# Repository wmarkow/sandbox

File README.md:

# sandbox
A sandbox reprository for my various projects.

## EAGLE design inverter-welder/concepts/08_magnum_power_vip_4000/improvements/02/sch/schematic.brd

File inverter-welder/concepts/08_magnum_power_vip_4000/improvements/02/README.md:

# Przeróbka spawarki Magnum Power VIP4000 na MIG

## Istota problemu: obniżenie napięcia biegu jałowego i napięcia spawania

Interesującym pomysłem jest przerobienie spawarki elektrodowej (MMA) na spawarkę typu MIG/MAG. Sprawa nie jest prosta gdyż spawarka
elektrodowa cechuje się sterowaniem prądowym (automat pilnuje nastawy pradowej) podczas gdy spawarki MIG/MAG pilnują nastawy napięciowej.
Z drugiej strony sprawa nie jest aż tak tragiczna i została poruszona w kilku miejscach, zwłaszcza na forum elektroda.pl na przykład
tutaj:

 * [Spawarka inwertorowa jako źródło migomatu?](https://www.elektroda.pl/rtvforum/topic688745.html)
 * [Spawarka mig mag z inwertera czy da rade ? ](https://www.elektroda.pl/rtvforum/topic1481430.html)
 * [Nakładka MIG do spawarki inwertorowej?](https://www.elektroda.pl/rtvforum/topic2955459.html)
 * [Poszukuję chętnego do przerobienia spawarki inwertorowej](https://www.elektroda.pl/rtvforum/topic2409633.html)
 * [dedra 200 przeróbka na miga czy możliwe jest zastosowanie te](https://www.elektroda.pl/rtvforum/topic959926.html)
 * [Przeróbka spawarki inwertorowej MMA na MIG-MAG](https://forum.elportal.pl/viewtopic.php?t=13849)

Kilku użytkowników forum wskazuje, że można spróbować podłączyć palnik MIG wraz z podajnikiem drutu bezpośrednio
do wyjścia spawarki elektrodowej i po prostu spróbować. Nie zawsze kończy się to sukcesem. Problemem okazuje się
również zbyt wysokie napięcie biegu jałowego w spawarkach elektrodowych, które mieści się w granicach 60-70V (zależy od
modelu urządzenia).
Tak wysokie napięcie powoduje szybkie upalanie się drutu spawalniczego, zwłaszcza w początkowej fazie spawania,
gdzie mechanizm regulacji prądowej nie zdążył jeszcze zareagować (regulacja prądu wyjsciowego odbywa sie na zasadzie
obniżenia napięcia wyjściowego: im niższe napięcie wyjsciowe tym mniejszy prąd na wyjsciu) i przez krótki moment do
drutu spawalniczego podłączone jest wysokie napięcie jałowe.
Sam dokonałem takiej próby: podłączyłem prowizoryczny palnik MIG typu SpoolGun (zbudowany na szybko tylko w celu wykonania doświadczenia).
Rzeczywiście, przy próbie spawania końcówka drutu bardzo szybko się rozgrzewa do czerwoności i upala się przy końcówce prądowej
palnika. Następuje wtedy stan rozwarcia, spawarka wykrywa brak przepływu prądu (bo drut nie styka się już
z materiałem spawanym) i przechodzi w tryb biegu jałowego, gdzie napięcie na wyjściu znów jest wysokie w ok. 60-70V. Po pewnej
chwili stale wysuwający się drut ponownie dotyka materiału spawanego, zaczyna przepływać prąd, drut się rozgrzewa (wysokie napięcie
jałowe), być może przez chwilę automat ogranicza na moment napięcie wyjsciowe by ustalić przepływ ustalonego prądu, ale często
jest już za późno, gdyż drut ponownie się upala przy końcówce prądowej, i cykl się powtarza. Generalnie nie idzie spawać.
Często się zdarza, że drut stapia się z końcówką prądową. Przestaje wtedy działać posów drutu a końcówka prądowa nadaje się
najczęściej do wymiany.

## Symulacja regulacji napięcia: układ z potencjometrem podłączonym do pinu 8 układu SG3525

Zainspirowany różnymi amatorskimi konstrukcjami spawarek MMA/MIG/MAG w szczególności [Invertor popis](https://github.com/wmarkow/sandbox/blob/master/inverter-welder/concepts/09_mma_mig_mag/invertor_popis.pdf),
postanowiłem podjąć kroki by mimo wszystko spróbować dokonać przeróbki spawarki elektrodowej inwertorowej na MIG/MAG. Moja spawarka **Magnum Power VIP 4000** jest
oparta o układ scalony **SG3525**. Po przejrzeniu [noty katalogowej](https://github.com/wmarkow/sandbox/blob/master/inverter-welder/elements/sg3525/SG1525.pdf) postanowiłem [zbadać jego zachowanie](https://github.com/wmarkow/sandbox/blob/master/inverter-welder/elements/sg3525/tests/README.md) w różnych układach konfiguracyjnych.
W kontekście obniżenia napięcia biegu jałowego szczególnie interesujący jest [Test 4: limit PWM duty cycle with Soft-Start pin](https://github.com/wmarkow/sandbox/blob/master/inverter-welder/elements/sg3525/tests/Test4/README.md),
gdzie wykorzystany został Pin 8 układu (tzw. Soft Start) do ograniczenia przebiegu PWM na wyjściu układu. To rozwiązanie jest godne uwagi ze względu na bezinwazyjność w układ sterowania spawarki; wystarczy wlutować jeden dodatkowy potencjometr. 

Schemat układu symulacji został przedstawiony na rysunku poniżej. Po lewej stronie znajduje się
orginalny układ spawarki: kondensator C32 i rezystor R40 podłączone do pinu 8 układu SG3525. Razem
z wewnetrznym źródłem prądowym 50uA realizują one układ tzw. "miękkiego startu". Dopóki napięcie
na pinie 8 jest mniejsze od 0.9V, dopóty ukłąd generuje sygnały PWM o wypełnieniu 0%. Gdy napięcie
jest wyższe od 3.3V to ukad generuje sygnały o wypełnieniu 49%. Poziomy napięć pomiędzy 0.9V a 3.3V
generują sygnały PWM o wypełnieniu od 0% do 49%. Tak rzecze dokumentacja układu SG3525. Po włączeniu
zasilania układ "miękkiego startu" powoli rozkręca układ do generacji maksymalnego wypełnienia.
Dodatkowym potencjometrem (schemat po prawej) można ustalić w miarę dowolne napięcie na pinie 8, 
co pozwoli z góry ograniczyć napięcie na biegu jałowym lub spawania. 

Symulacja pokazuje wpływ takiego rozwiązania na układ "miękkiego
startu". Wykres napięć w obu przypadkach (bez modyfikcji kolor zielony i z modyfikacją kolor niebieski) poniżej:

pokazuje, że modyfikacja spowalnia rozruch urządzenia prawie dwukrotnie (na maksymalnym ustawieniu potencjometru):
* bez modyfikacji układ osiąga PWM 49% (napięcie 3.3V) po około 45ms. Kondensator ładuje się liniowo ze źródła prądowego.
* z modyfikacją układ osiąga PWM 49% (napięcie 3.3V) po około 75ms. Ponadto obecność potencjometru zmienia charakterystykę ładowania
kondensatora z liniowej na wykładniczą.

Wydaje mi się, że takie spowolnienie nie ma negatywnego wpływu na pracę urządzenia. Gorzej by było,
gdyby modyfikacja przyspieszyła rozruch.

## Próba z potencjometrem podłączonym do pinu 8 układu SG3525

Zmontowany układ pomiarowy wygląda tak:

Na zdjęciu widać podlutowany odpowiednio potencjometr (wartość 88k zmierzona miernikiem), zaciski prądowe, multimetr i ... podłączoną do zacisków żarówkę.
Żarówka wstępnie obciąża układ względnie niską rezystancją. Występuje na niej napięcie ok 61V i przepływa
przez nią prąd ok 50mA (przy potencjometrze ustawionym na wartość maksymalną) [^1]. Bez tej żarówki napięcie wyjściowe na zaciskach jest mniej więcej stałe i wynosi około
62V bez wględu na wartość nastawy potencjometru. Innymi słowy wartość wypełnienia generowanego sygnału PWM się zmienia, ale napięcie
na wyjściu **wskazywane multimetrem** (to jest ważne) jest stałe. Okazuje się, że spawarka w obwodzie wyjściowym
ma kondensatory, które są ładowane ze źródła. Wyjście spawarki jest już "wstępnie obciążone" dzielnikiem
rezystancyjnym (o wartości 23.4k) służącym do pomiaru napięcia wyjściowego i wykrywania stanu zwarcia elektrody.
Ten dzielnik rezystancyjny powoduje powolne rozładowanie kondensatorów wyjściowych, dlatego napięcie wskazywane
przez multimer jest mniej więcej stałe bez względu na wartość wypełnienia sygnału PWM; napięcie zauważalnie maleje dopiero przy niskich
wypełnieniach PWM. Podłączona żarówka ma za zadanie wstępnie obciążyć układ małą rezystancją (małą w porównaniu
z dzielnikiem napięcia ale wysoką od rezystancji łuku spawalniczego), co spowoduje szybsze rozładowanie kondensatorów i multimetr "zauważy" spadek napięcia
wyjściowego.
  
Nastawę potencjometru określiłem sobie w godzinach, zgodną z tarczą wskazówek zegarka, jak na zdjęciu poniżej:

Wyniki pomiarów znajdują się w tabelce poniżej:

 | Nastawa potencjometru [h] | Zmierzone napięcie wyjściowe przy rozłączonej żarówce [V] | Zmierzone napięcie wyjściowe przy załączonej żarówce [V]| Zmierzone napięcie na potencjometrze [V]| Zmierzona oporność na potencjometrze [kOhm]| Obliczony PWM [%]| Obliczone napięcie wyjściowe [V]|
 |---|---|---|---|---|---|---|
 |   max | 61.9 | 60.4 | 3.7 | 88.5 | 49 | 62 |
 |    15 | 61.4 | 59.5 | 3.1 | 74.6 | 45 | 57 |
 |    12 | 59.8 | 53.7 | 1.8 [^2] | 39.6 | 18 | 23 |
 |    11 | 59.7 | 52.4 | 1.5 | 34.0 | 12 | 15 |
 | 11/10 | 20.0 |  8.9 | 1.2 | 27.8 |  6 |  8 |
 |    10 | 10.0 |  0.0 | 0.9 | 19.9 |  0 |  0 |
 |     9 | 10.0 |  0.0 | 0.6 | 11.5 |  0 |  0 |
 |   min | 10.0 |  0.0 | 0.0 |  |  0 |  0 |

Potencjometr okazuje się działać ale jednak nieliniowo. Bardzo łatwo jest zbić napięcie do zmierzonej wartości około 45V. Później
dalsza minimalna zmiana nastawy skutkuje szybkim spadkiem napięcia do 0V. Udało mi się uzyskać zmierzone napięcie wyjściowe
35V a potencjometr był ustawiony wtedy na 27.5k (nastawa gdzieś pomiędzy godziną 10 a 11).

Nadmienię jeszcze raz fakt pomiaru napięcia multimetrem. Przy rozłączonej żarówce multimetr nie zauważa zbytniego spadku napięcia
wyjściowego. Jest to spowodowane obecnością dużej wstępnej rezystancji obciążającej (23.4k) układ i powodującej
powolne rozładowywanie kondensatorów wyjsciowych. Przy załączonej żarówce o oporności około nieco ponad 1k multimetr
łatwiej zauważa spadek napięcia wyjściowego. Jednak ten pomiar multimetrem równiez należy traktować tylko jako **pomiar
orientacyjny!** Prawdziwa wartość napięcia ujawnia się dopiero podczas procesu spawania, gdzie rezystancja obciążenia jest
na prawdę niska i prawie bliska rezystancji zwarciowej. Dlatego w tabelce powyżej zamieściłem kolumny pomocnicze:
* **PWM** zawierającą wyliczoną - na podstawie napięcia na pinie 8 układu SG3525 - wartośc wypełnienia genarowanych
sygnałów PWM. Wartość 49% oznacza generowanie maksymalnego napięcia (ok. 62V), wartość 0% oznacza minimalne
napięcie na wyjściu (ok 0V).
* **Obliczone napięcie wyjściowe** - wyznaczone na podstawie wartości wypełnienia **PWM**. Wartość tego napięcia
należałoby traktować jako wyrocznię, gdyż ta wartość ujawnia się podczas procesu spawania.

Widać, że regulacja napięcia biegu jałowego działa. Trzeba by wykonać próbę spawania. Aby polepszyć zakres
regulacyjny potencjometru, proponuję zamienić go na opornik około 33k połączony szeregowo z potencjometrem 
o wartości ok. 56k. Powinno być wtedy możliwe bardziej selektywne regulowanie napięcia biegu jałowego w zakresie ok. 15V-60V.
Warto by było przeprowadzić test ze zmniejszoną opornością obciążenia wstępnego (żarówki). W przeprowadzonym teście żarówka miała opór
ciut większy od 1k, być może warto by było zastosować tutaj jakiś rezystor dużej mocy o oporności np. 200 Ohm?

Ciekawostką jest fakt, że przy rozłączonej żarówce i napięciu na pinie 8 mniejszym od 0.9V, napięcie zmierzone na wyjściu spawarki jest 10V.
Dopiero przy załączonej żarówce spada do 0V.

## Pierwsze testowe spoiny

Na potrzeby testu zbudowałem prowizoryczny uchywt typu spool-gun:

Jest bardzo nieporęczny ale daje radę podczas testów. W skład konstrukcji wchodzą:
* końcówka palnika wraz z końcówką prądową przymontowane taśmą do długiej na ok. 40cm pilśniowej listwy. Do tej końcówki bezpośrednio
jest "zapięty" uchwyt elektrodowy podłączony do zacisku masowego spawarki, gdyż spawanie odbywa się z użyciem drutu proszkowego, gdzie producent zaleca,
że drut musi być podpięty do zacisku masowego. 
* podajnik drutu zrobiony z silnika krokowego NEMA 17 i ekstrudera filamentu od drukarki 3D. Silnik krokowy zapewnia odpowiedni posuw drutu. Ekstruder posiada
koło zębate (założone bezpośrednio na wał silnika) oraz element dociskowy z małego łożyska. Generalnie okazuje się to działać poprawnie. Minusem rozwiązania
jest zbyt duża waga silnika zwiększająca ciężar całego uchwytu.
* szpulka z drutem założona bezpośrednio na wkręconą w pilśniowa listwę śrubę M8. Szpulka zabezpieczona jest przed wypadnięciem nakrętką M8.
* wyłącznik krańcowym służy jako włącznik podajnika drutu
* Arduino UNO wraz z "nakładką CNC" reaguje na naciśnięcie wyłącznika krańcowego i steruje wtedy silnikiem krokowym
* potencjometr zamontowany do "nakładki CNC" służący do regulacji szybkości posuwu drutu w zakresie od 0 do 200 cm/min. 

Pierwsze próby pięciu spoin na zdjęciach poniżej. Generalnie zaczynałem od minimalnej nastawy napięcia 35V (uwaga: wartość zmierzona multimetrem - traktować tylko orientacyjnie ze względu na niedostatecznie niską
rezystancję żarówki) i minimalnej nastway prądu 100A.
Prędkość wysuwu drutu szybko ustawiłem na 200cm/min, gdyż przy mniejszych wartościach wysuwu wychodziły tylko poprzerywane krople (z prawej strony
zdjęć). Próba numer 1 okazała się mieć za niskie napięcie lub za niski prąd. Przy próbce 2 już zwiększyłem nastawę prądu do 140A. Nastawy
napięcia niestety nie zanotowałem. Generalnie przy kolejnych próbach zacząłem zwiększać nastawy prądu i napięcia,
aż przy próbce numer 4 i 5 spoina zaczęła się wtapiać w materiał podstawowy. Z lewej strony nieudolnie wspawana nakrętka.

## Kolejne testowe spoiny

Po pierwszych próbach testowych ponownie obejrzałem filmik na Youtube [How NOT TO Weld: Most Common MIG Welding Mistakes](https://www.youtube.com/watch?v=Xod-ByrxHg4), 
objaśniający podstawowe typy błędów w spawaniu MIG. Skupiłem się na prędkości wysuwu drutu spawalniczego. Optymalną prędkością na filmiku była 200 cali/min (czyli ok 500 cm/min),
podczas gdy ja używałem tylko 200 cm/min. Zmodyfikowałem program Arduino i już pseudo spool-gun był gotowy do pracy z wysuwem drutu w zakresie 0-500 cm/min.
Zdjęcia spoin testowych poniżej:

Prąd spawania ustawiłem na 200A (maksymalna nastawa spawarki) a napięcie biegu jałowego ograniczone zostało potencjometrem
do poziomu 55V (uwaga: wartość zmierzona multimetrem - traktować tylko orientacyjnie ze względu na niedostatecznie niską
rezystancję żarówki). Obliczona wartość napięcia wyjściowego dla tej nastawy - według tabelki powyżej - byłaby około 30V. Tym razem spoiny wyglądaja dużo lepiej. Widać wtopienie w materiał podstawowy. Próby 1 i 2 szły bez problemu.
W próbie 3 postanowiłem zmniejszyć nastawę prądu do 100A i zacząłem odczuwać odpychanie uchwytu od materiału podstawowego.
Prawdopodobnie zbyt niski prąd nie nadążał topić drutu wysuwanego z tak dużą prędkością. Średnia długość spoin na zdjęciach
to około 3-4 cm. Funkcja anti-stick spawarki wydawała się nie mieć negatywnego wpływu na proces spawania; na razie nie widzę 
potrzeby rozłączania tego mechanizmu podczas spawania MIG.

## Symulacja regulacji napięcia: układ ze sprzężeniem zwrotnym podłączony do pinu 8 układu SG3525

Ciekawy układ regulacji napięcia wyjściowego został przytoczony w [tym poście na forum](https://www.elektroda.pl/rtvforum/viewtopic.php?p=19978221#19978221).
Schemat zaczerpnięty prawdopodobnie z rosyjskojęzycznej strony Internetu:

Kilka słów wyjasnienia:
* zaciski K+ i K- to najprawdopodobniej zaciski wyjściowe spawarki
* potencjometr 10k służy do nastawy napięcia wyjściowego
* przełącznik MMA/MIG-MAG służy do przełączania sterownika w tryb MMA lub MIG-MAG
* przekaźnik na dole po lewej jest załączany przyciskiem w uchwycie MIG. W stanie normalnym przycisk nie jest wciśnięty
(nie ma spawania) i wyjście przekaźnika zwiera pin 8 układu SG3525 do masy i napięcie na wyjściu spawarki jest 0V. Po wciśnięciu
przycisku w uchwycie (rozpoczęcie procesu spawania) przekaźnik się załącza i odcina pin 8 od masy, następuje włączenie napięcia
spawania.
* optoizolator PC817 zapewnia izolację galwaniczna pomiędzy obwodem spawania a obwodem sterowania SG3525, a jednocześnie steruje
napięciem na pinie 8

Przygotowałem symulację tego układu w programie LTSpice. Schemat układu jest następujący:

Symulacja układu polega na wymuszonej zmianie napięcia spawania w zakresie od 0 do 60V i obserwacji jej wpływu na napięcie pinu 8.
Wynik symulacji przedstawia sie następująco:

Analiza:
* potencjometr nastawy napięcia ustawiony w pozycji środkowej (nastawa na 30V)
* jeżeli napięcie spawania spadnie poniżej ok. 29V to napięcie na pinie 8 jest 5V, co spowoduje generowanie sygnałów
PWM o wypełnieniu 49% i wzrost napięcia wyjściowego w kierunku wartości maksymalnej 60V
* jeżeli napięcie spawania wzrośnie powyżej ok. 29V to napięcie na pinie 8 jest 0V, co spowoduje generowanie sygnałów
PWM o wypełnieniu 0% i spadek napięcia wyjściowego w kierunku wartości minimalnej 0V
* w układzie wystepuje sprzężenie zwrotne, które dąży do ustabilizowania napięcia na zadanym poziomie
* stabilizacja napięcia jest raczej dwustabilna: albo spawarka podaje napięcie maksymalne albo minimalne. Takie cykliczne
zmiany stabilizują napięcie wyjściowe na średnim zadanym poziomie. Nasuwa się pytanie czy taki dwustabilny tryb pracy jest
dobry dla procesu spawania lub spawarki. Można przecież wysterować pin 8 napięciem pośrednim (np. 2.5V) co wygeneruje
pośrednie napięcie spawania.
* na powyższym wykresie tego nie widać, ale regulacja napięcia wyjściowego jest w zakresie od 20 do 40V.

Powyższego układu nie testowałem w praktyce. Tylko zasymulowałem jego działanie.

## Ciekawostka:
* test z wyłączoną żarówką
  * wyłączyć spawarkę
  * upewnić się, że żarówka jest wykręcona
  * upewnić się, że potencjometr biegu jałowego jest ustawiony w pozycję maksymalną (czyli nie działa ograniczanie napięcia biegu jałowego)
  * włączyć spawarkę
  * zmierzyć miernikiem napięcie na zaciskach wyjściowych: u mnie było ono 61V
* test z włączoną żarówką
  * wyłączyć spawarkę
  * upewnić się, że żarówka jest wkręcona
  * upewnić się, że potencjometr biegu jałowego jest ustawiony w pozycję maksymalną (czyli nie działa ograniczanie napięcia biegu jałowego)
  * włączyć spawarkę
  * zmierzyć miernikiem napięcie na zaciskach wyjściowych: u mnie było ono 0V!
  * wykręcić żarówkę (żeby nie obciążać nią wyjścia spawarki)
  * wkręcić żarówkę ponownie
  * zmierzyć miernikiem napięcie na zaciskach wyjściowych: teraz było ono 61V!
 
Wygląda, jakby układ spawarki wykrywał, że podczas jej uruchomienia było podłączone jakieś obciążenie; w takim przypadku - prawdopodobnie - układ SG3225 jest w stanie
zamknięcia (odcięcia) i generuje on sygnał PWM o zerowym wypełnieniu. Być może jest to jakieś dodatkowe zabezpieczenie. W tym konkretnym przypadku, żadne diody sygnałowe
na panelu urządzenia nie były zapalone.

[^1]: Co by wskazywało, że opór podłączonej żarówki jest 1.22k
[^2]: Napięcie na potencjometrze jest jednocześnie napięciem na pinie 8 układu SG3525. Napięcie 1.8V generuje
sygnał PWM o wypełnieniu około 18%, co powinno generować napięcie 22V. Tymczasem multimetr wskazuje zawyżone napięcie 53.7V.
Być może oporność żarówki 1.22k jest jeszcze zbyt duża i wyjście spawarki nie jest dostatecznie szybko rozładowywane?

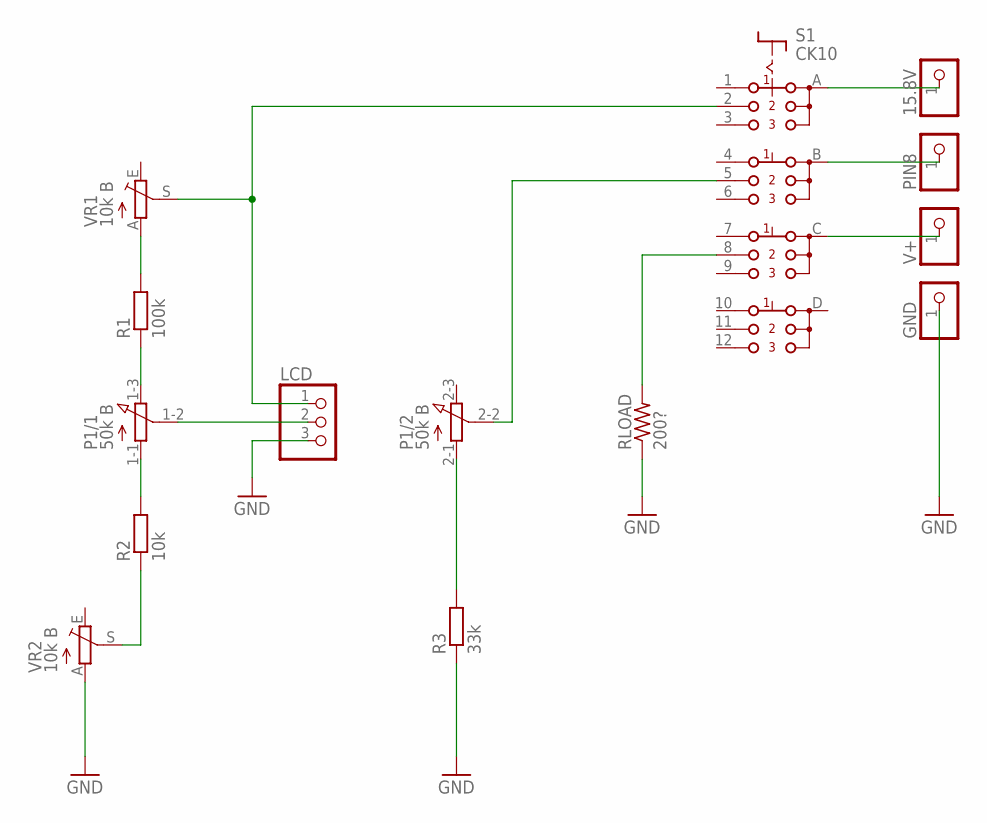
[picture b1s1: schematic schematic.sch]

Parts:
15.8V: PINHD-1X1; 1X01
GND: PINHD-1X1; 1X01
LCD: PINHD-1X3; 1X03
P1: 50k B; 3RP/1610G
PIN8: PINHD-1X1; 1X01
R1: 100k; 0204/5
R2: 10k; 0204/5
R3: 33k; 0204/5
RLOAD: 200?; VTA52
S1: CK10
V+: PINHD-1X1; 1X01
VR1, VR2: 10k B; RJ9W

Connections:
GND: GND.1, LCD.3, R3.1, RLOAD.1, VR2.A
unnamed: P1.2-2 (S), S1.5 (B2)
unnamed: 15.8V.1, S1.A
unnamed: PIN8.1, S1.B
unnamed: P1.1-1 (A), R2.2
unnamed: P1.1-3 (E), R1.1
unnamed: LCD.1, S1.2 (A2), VR1.S
unnamed: R1.2, VR1.A
unnamed: LCD.2, P1.1-2 (S)
unnamed: R2.1, VR2.S
unnamed: S1.C, V+.1
unnamed: RLOAD.2, S1.8 (C2)
unnamed: P1.2-1 (A), R3.2

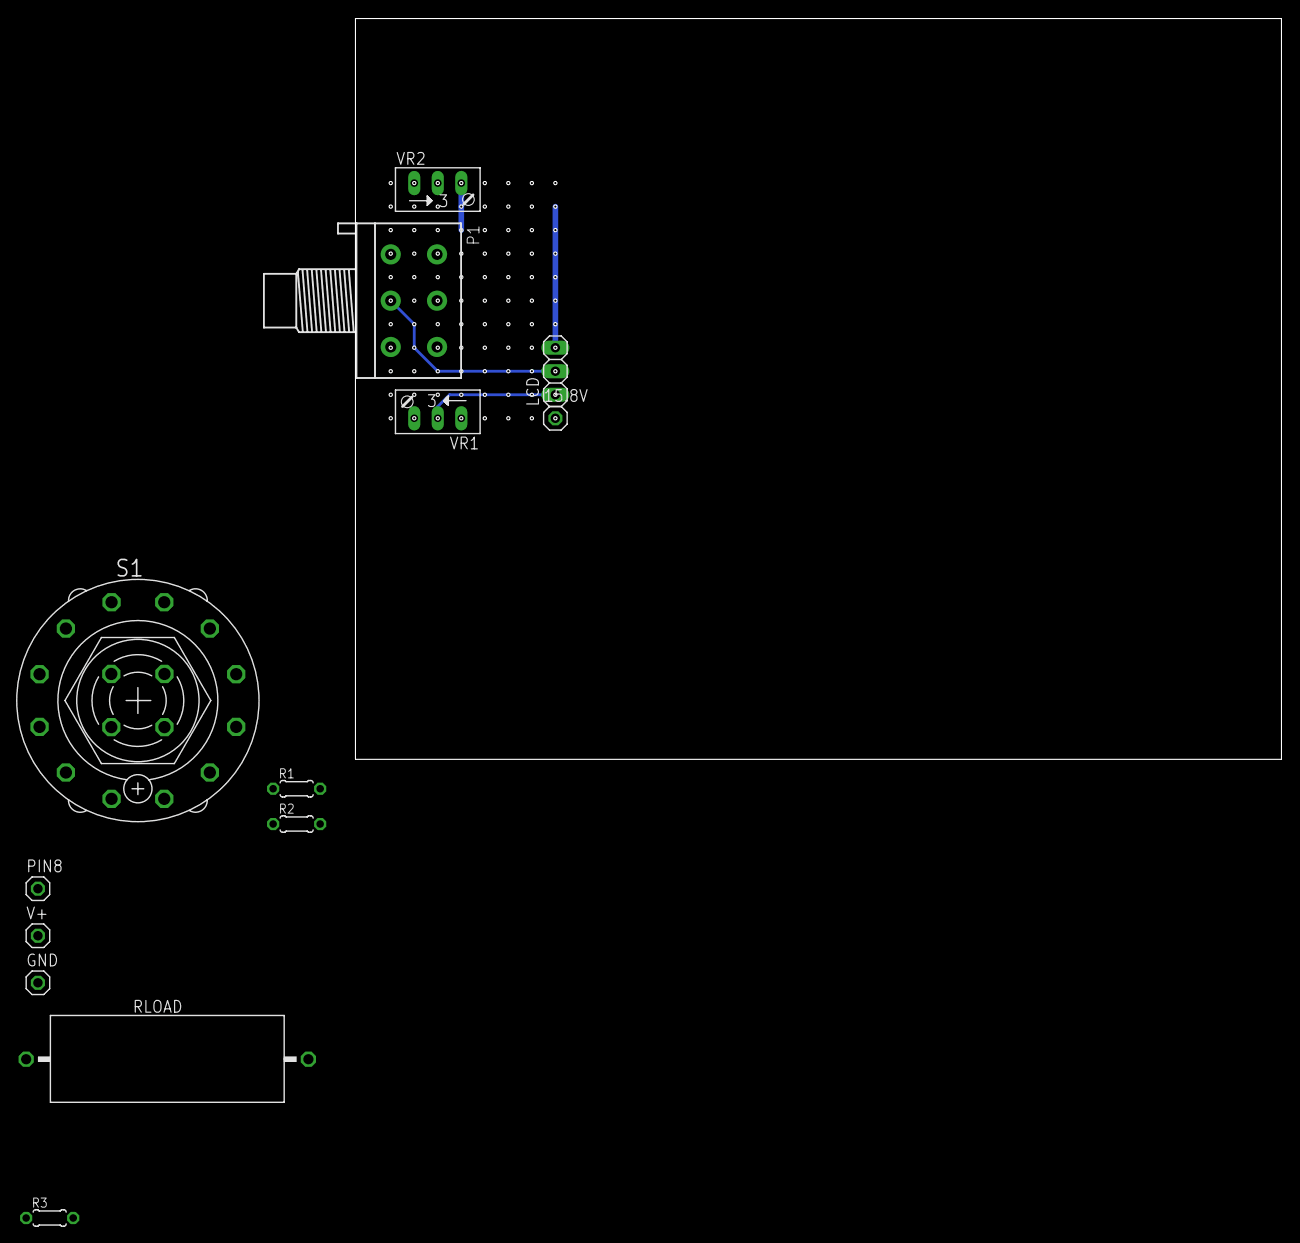
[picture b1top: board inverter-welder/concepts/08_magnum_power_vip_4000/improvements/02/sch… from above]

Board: 2 copper layers, 100.0 x 80.0 mm, 13 parts (0 on the bottom side), 13 nets.

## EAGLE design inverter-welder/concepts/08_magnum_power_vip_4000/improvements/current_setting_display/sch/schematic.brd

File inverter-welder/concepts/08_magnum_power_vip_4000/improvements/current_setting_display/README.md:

# Przeróbka spawarki Magnum Power VIP4000: dodanie wyświetlacza panelowego

Postanowiłem wzbogacić moją spawarkę o wyświetlacz panelowy, który wyświetlałby aktualną nastawę prądu spawania. Sam potencjometr ze skalą w zasadzie wystarczy
ale jak się później okazało, wyświetlacz ma również swoją zaletę: można precyzyjniej ustawić wartość prądu spawania. Pewnego razu musiałem używać na zmianę
elektrod o grubości 1.6mm i 2.0mm. Eksperymentalnie doszedłem do wniosku, że w tej konkretnej aplikacji elektrodą 1.6mm spawa mi się najlepiej prądem ok 33A
a do elektrody 2.0mm potrzebuję prądu spawania 45A. Wyświetlacz panelowy bardzo ułatwił mi przełączanie się pomiędzy elektrodami. Polegając tylko na samej skali
potencjometru nie byłbym w stanie uzyskać tych dwóch konkretnych nastaw prądu.

Zastosowany wyświetlacz dla kilku nastaw przedstawia się następująco:

a zamontowany w spawarce układ wygląda tak:

<br/>

## Idea układu
Rozwiązanie techniczne wyświetlacza polega na zastąpieniu orginalnego potencjometru nastawy potencjometrem podwójnym oraz użyciu prostego woltomierza panelowego:
* pierwszy ślizgacz potencjometru służy do regulacji nastawy prądu i jest bezpośrednio wmontowany w układ spawarki (zamiast potencjometru orginalnego)
* drugi ślizgacz służy do wyświetlania wartości nastawy na woltomierzu panelowym

Ponieważ oba ślizgacze są regulowane jednocześnie za pomocą tej samej gałki to mamy pewność, że nastawa prądu jest zgodna z tym co przedstawia woltomierz panelowy. Układ został tak skalibrowany,
że przy nastawie minimalnej wyświetlacz pokazuje napięcie **0.20V** (co odpowiada nastawie 20A) a przy nastawie maksymalnej wyświetlacz pokazuje **2.00V** (co odpowiada
nastawie 200A). Skalibrowane nastawy bazują jedynie na tabliczce znamionowej podanej przez producenta. Nie ma pewności, że nastawa 200A rzeczywiście ustawia prąd spawania
na poziomie 200A, jednakże powtarzalność nastaw jest tutaj zapewniona. Oczywiście można wyświetlacz skalibrować również za pomocą cęgowego miernika prądu.

Przed przystąpieniem do prac dokonałem oględzin orginalnego potencjometru i jego okolic. Poniżej schemat układu, uzyskany metodą inżynierii odwrotnej:

Potenjometr nastawy (VRa + VRb) ma wartość **830** ohm a jego zaciski sa podłączone do trzech przewodów w kolorach czerwonym (przez VR1 i R79 do zasilania 15.8V), czarnym (wyjście nastawy) i zielonym (do masy).
Przewód czarny idzie bezpośrednio przez rezystory R71 i R55 a potem dalej do wzmacniacza operacyjnego, który odpowiedzialny jest za utrzymanie prądu spawania podczas procesu spawania.
Poniżej przedstawiam wartość napięcia na wyjściu potencjometryu (przewód czarny) w zależności od nastawy potencjometru:

 | Nastawa prądu [A] | Napięcie na wyjściu potencjometru (przewód czarny) [V] |
 |---|---|
 | min | 0.00 |
 |  20 | 0.00 |
 |  65 | 1.90 |
 | 110 | 3.53 |
 | 145 | 5.15 |
 | 200 | 6.48 |
 | max | 6.59 |

Projektując układ wyświetlacza należy za pomoca nowego potencjometru uzyskać takie same poziomy napięć na przewodzie w kolorze czarnym, wtedy układ nastawy będzie działał taki sam sposób, jak przewidział to producent.
Dobór odpowiednigo potencjometra podwójnego nie jest prosty; trzeba użyć potencjometru o wartości jak najbardziej zbliżonej do orginalnej. Na przykład użycie takiego o wartości 10k powoduje generowanie
dużo wyższych napięć, co spowoduje niepoprawną pracę urządzenia. Taki o wartości **830** ohm był dla mnie nieosiągalny i dlatego zdecydowałem się na najprostszy (co nie oznacza, że najlepszy) 
potencjometr **1k** jak na zdjęciu poniżej:

<br/>

## Schemat układu
Schemat nowego potencjometru nastawy wraz z wyświetlaczem panelowym poniżej:

**P1/2** to ślizgacz potencjometru wmontowanego bezpośrednio w spawarce zamiast orginalnego potencjometru. Ponieważ użyty przeze mnie potenjometr podwójny ma wartość **1k** (a orginalny
ma wartość **830** ohm), używam potencjometru VR3 o wartości **500** ohm by dostosować charakterystykę nowego potencjometru do tego orginalnego. Chodzi o to by przy minimalnej nastawie
uzyskać napięcie czarnego przewodu na poziomie 0.00V a przy maksymalnej nastawie uzyskać napięcie około 6.60V.

Potencjometr **P1/1** i rezystory nastawne **VR1** i **VR2** służą do regulcaji i wyświetlania napięcia na woltomierzu panelowym. VR1 i VR2 należy tak wyregulować aby:
* przy minimalnej nastawie woltomierz pokazywał **0.20** V
* przy maksymalnej nastawie woltomierz pokazywał **2.00** V

Montaż układu jest prosty:
* VR1 ustawić na wartość maksymalną 10k
* VR2 ustawić na wartość minimalną 0 ohm
* P1/1 ustawić na wartość maksymalną 1k
* VR3 ustawić na wartośc maksymalną 500 ohm
* podłączyć odpowiednio wyjścia złącza JP1 do przewodów w spawarce (zielony, czarny i czerwony). Zasilanie 15.8V znaleźć w spawarce za pmoocą woltomierza.
* podłączyć odpowiednio woltomierz panelowy do złącza LCD

<br/>

## Kalibracja trymera VR3:
1. uruchomić spawarkę
2. ustawić maksymalną nastawę prądu (200A)
3. zmniejszać wartość trymera VR3 aż do uzyskania napięcia na czarnym przewodzie na poziomie 6.60V
4. ustawić minimalną wartość nastawy prądu; napięcie na czarnym przewodzie powinno wynosić 0V

<br/>

## Kalibracja wyświetlacza:
1. uruchomić spawarkę
2. ustawić maksymalną nastawę prądu (200A)
3. zmieniać (generalnie zmniejszać) wartość trymera VR1 aż woltomierz pokaże 2.00V
4. ustawić minimalną nastawę prądu spawania (20A)
5. zmieniać (generalnie zwiększać) wartośc trymera VR2 aż woltomierz pokaże 0.20V
6. powtórzyć kroki od 2 do 5 kilka razy (zwykle 3 razy są wystarczające)
7. przy minimalnej nastawie woltomierz powinien pokazać 0.20 a przy maksymalnej nastawie powinien pokazać 2.00

W tym momencie wyświetlacz jest skalibrowany i powinien działać poprawnie. Mi przeszkadzała jeszcze kropka dziesiętna w woltomierzu panelowym. Aby jej nie wyświetlać to należy
przeciąć nóżkę sterującą (pin 3) w wyświetlaczu siedmiosegmentowym i złatwione (schemat [tutaj](https://raw.githubusercontent.com/wmarkow/sandbox/master/inverter-welder/concepts/08_magnum_power_vip_4000/improvements/current_setting_display/docs/3_digits_display.jpg)).
Z kropką dziesiętną wyświetlacz pokazuje tak:

natomiast bez kropki jest już o niebo lepiej:

<br/>

## Niedoskonałość skali
Jeszcze jedna uwaga o pewnej niedoskonałości całego rozwiązania: mianiowicie wskazania wyświetlacza nie pokrywają się ze wskazaniami orginalnej skali potencjometru. Wynika to z tego, że zastosowany
przeze mnie potenjometr ma większy kąt obrotu niż potencjometr orginalny. Być może można by coś w tej sprawie polepszyć, np. zastosować jakiś mechaniczny ogranicznik kątu obrotu uniemożliwiający dokonanie
pełnej nastawy potencjometru. Ponadto zastosowany potencjometr ma "ząbkowaną" oś (patrz zdjęcie powyżej) a gałka potencjometru zaciskana jest na śrubkę, w efekcie czego dokręcając ową śrubkę gałka 
zawsze przekręca się o pewien mały kąt i chce by śrubka dociskała się zawsze pomiędzy dwa sąsiednie ząbki.

<br/>

## Wyznaczanie wartości trymerów VR1 i VR2

Wartości trymerów VR1 i VR2 wyznacza się na podstawie dwóch granicznych położeń potencjometru nastawy prądu:
 * dla nastawy minimalnej wartość prądu spawania jest 20A a woltomierz powinien wtedy wskazywać napięcie 0.20V
 * dla nastawy maksymalnej wartość prądu spawania jest 200A a woltomierz powinien wtedy wskazywać napięcie 2.00V 

Oba przypadki zostały rozrysowane na schematach poniżej:

Rozpisujemy układ trzech równań:
 * równanie (1) określa prąd płynący w obwodzie - taki sam w obu przypadkach. Zakładamy, że woltomierz posiada dużą impedancję wejściową i przez niego praktycznie nie płynie żaden prąd.
 * równanie (2) określa wartość napięcia wskazywanego przez woltomierz dla minimalnej nastawy prądu spawania
 * równanie (3) określa wartość napięcia wskazywanego przez woltomierz dla maksymalnej nastawy prądu spawania

Rozwiązując ten układ równań można otrzymać dokładne wartości trymerów VR1 i VR2. Mamy tu teraz do czynienia wyłącznie z problemem matematycznym.
Można ułatwić sobie zadanie i rozwiązać je z inżynieryjnego punktu widzenia, co znacznie ułatwia obliczenia. Analizując układ można zauważyć,
że prąd płynący w układzie będzie miał wartość conajwyżej kulkunastu miliamperów, a napięcie na woltomierzu przy minimalnej nastawie prądu spawania jest małe (0.20V).
Fakt ten sugeruje, że wartość trymera VR2 będzie mała (kilkadziesiąt omów). Rozpatrując przypadek maksymalnej nastawy prądu spawania,
można by zaniedbać wartość trymera VR2 i na tej podstawie bardzo łatwo wyznaczyć przybliżoną wartość VR1. Znając wartość tej rezystancji
można przejść do przypadku minimalnej nastawy prądu i wyznaczyć przybliżoną wartość VR2. Odpowiednie wzory zostały przedstawione na grafice poniżej:

Podstawiając konkretne wartości liczbowe otrzymujemy wartości jak na rysunku poniżej:

Jako VR1 został wybrany trymer 10kohm, dla VR2 trymer o wartości 500ohm. Oba trymery w wersji wieloobrotowej, co umożliwia dokładną kalibrację układu wyświetlającego nastawę prądu spawania.

<br/>

## Materiały dodatkowe:
 * [schemat w formacie EAGLE](https://github.com/wmarkow/sandbox/tree/master/inverter-welder/concepts/08_magnum_power_vip_4000/improvements/current_setting_display/sch)
 * [symulacje układu w LTspice XVII](https://github.com/wmarkow/sandbox/tree/master/inverter-welder/concepts/08_magnum_power_vip_4000/improvements/current_setting_display/sim)

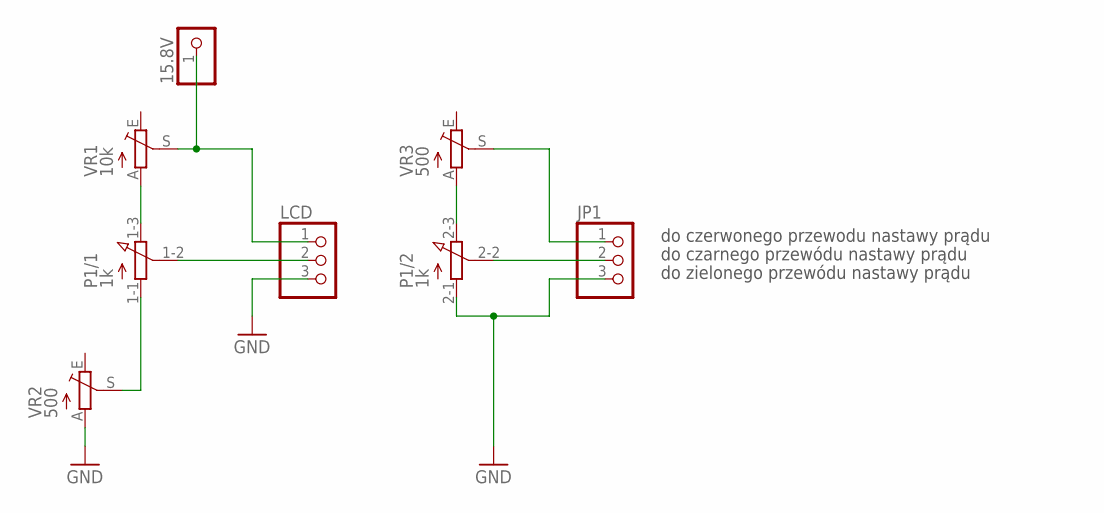
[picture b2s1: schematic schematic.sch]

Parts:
15.8V: PINHD-1X1; 1X01
JP1: PINHD-1X3; 1X03
LCD: PINHD-1X3; 1X03
P1: 1k; 3RP/1610G
VR1: 10k; RJ9W
VR2, VR3: 500; RJ9W

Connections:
GND: JP1.3, LCD.3, P1.2-1 (A), VR2.A
unnamed: P1.2-3 (E), VR3.A
unnamed: JP1.1, VR3.S
unnamed: JP1.2, P1.2-2 (S)
unnamed: P1.1-1 (A), VR2.S
unnamed: P1.1-3 (E), VR1.A
unnamed: 15.8V.1, LCD.1, VR1.S
unnamed: LCD.2, P1.1-2 (S)

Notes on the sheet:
do czerwonego przewodu nastawy prądu
do czarnego przewódu nastawy prądu
do zielonego przewódu nastawy prądu

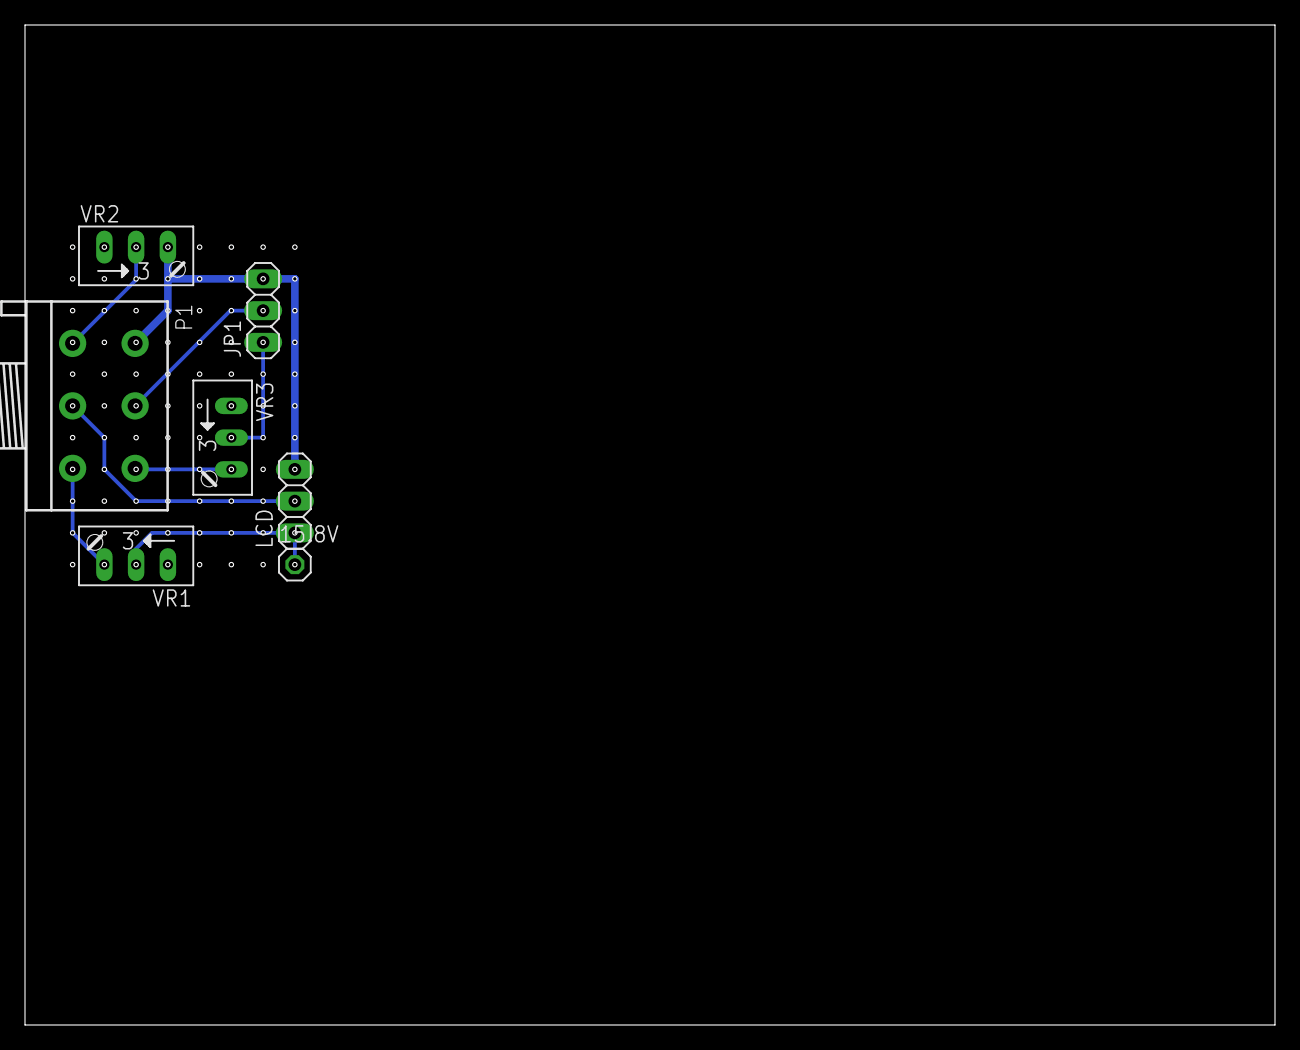
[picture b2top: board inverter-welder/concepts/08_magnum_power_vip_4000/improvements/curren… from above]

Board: 2 copper layers, 100.0 x 80.0 mm, 7 parts (0 on the bottom side), 8 nets.

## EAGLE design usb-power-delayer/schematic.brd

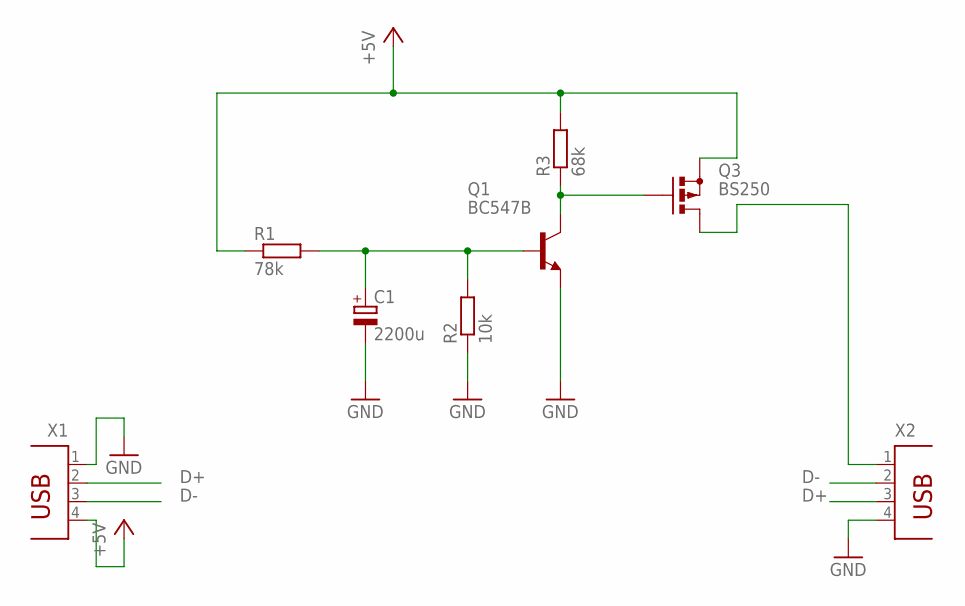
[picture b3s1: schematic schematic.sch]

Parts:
C1: 2200u; E3,5-8
Q1: BC547B; TO92
Q3: BS250; SOT54E
R1: 78k; 0204/5
R2: 10k; 0204/5
R3: 68k; 0204/5
X1, X2: PN87520

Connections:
+5V: Q3.S, R1.1, R3.2, X1.4
D+: X1.2, X2.3
D-: X1.3, X2.2
GND: C1.-, Q1.1 (E), R2.1, X1.1, X2.4
unnamed: C1.+, Q1.2 (B), R1.2, R2.2
unnamed: Q1.3 (C), Q3.G, R3.1
unnamed: Q3.D, X2.1

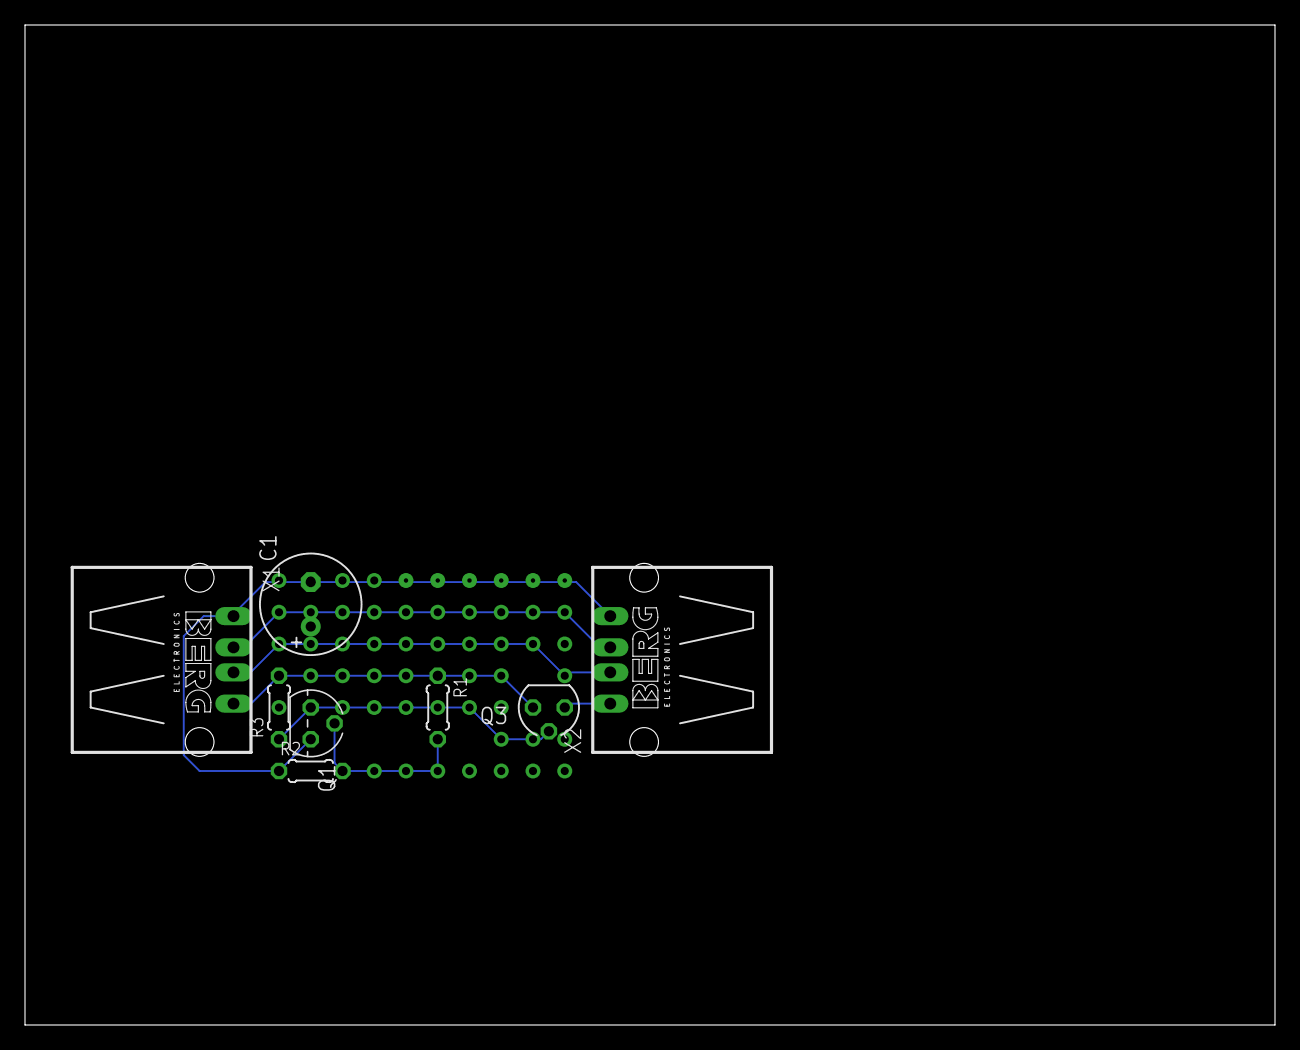
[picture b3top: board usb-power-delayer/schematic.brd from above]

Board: 2 copper layers, 100.0 x 80.0 mm, 8 parts (0 on the bottom side), 7 nets.

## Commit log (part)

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2020-02-14 Add usb-power-delayer
2020-02-14 Add some tests for HC12 wireless module.
2020-02-14 Something about motorcycle carburetors
2020-03-15 Add pictures of usb power delayer.
2020-03-15 Add some picture for fixing Esperanza induction cooker.
2020-03-29 Introduce Atx Bench Power Supply project. Add circuit for absolut value meassurement.
2020-05-21 Pictures of what can go bad by desk manufacture.
2020-05-21 Update README.md
    Embed images into readme.md
2020-05-21 Add an image how the desk should look like.
2020-05-21 Update README.md
    Embedd the image, how the desk should look like.
2020-05-21 Update README.md
    Fix readme
2020-05-21 Update README.md
    Fix typo in readme.
2020-06-04 [Welder]Add some info about welders.
2020-06-09 [Distiller] Add some photos how I winded the coil.
2020-06-09 [Welder] More informations in the topic of welding machines.
2020-06-09 [Welder] Add new concept from AVT.
2020-06-09 Remove Eagles *.b#* and *.s#* files as they are just a backup files.
2020-06-09 Add Eagles backups .b#* and .s#* and .l#* to gitignore.
2020-06-13 [Welder] Add SG3525 datasheet by Onsemi.
2020-06-13 [Welder] Add SG3525 basic simulation circuit.
2020-06-14 [Welder] Improve LYSpice simulation.
2020-06-15 [Welder] 3-input comparator explained.
2020-06-26 [Welder] Add some basic simulations of SG3525.
2020-06-27 [Welder] Reverse engineering of Magnum Power VIP 4000.
2020-06-27 [Welder] Add information where the MCR100-6.sub was downlaoded from.
2020-06-27 [Welder] More in the simulation of Magnum Power VIP 4000
2020-06-28 [Welder] Fix Led diodes on panel.
2020-06-28 [Welder] Improve pin8 simulation. Introduce parameters. Add some comments.
2020-06-28 [Rangefinder] Add some Excel for rangefinder calculations.
2020-07-01 [Welder] Simulation of short-circuit and possible of anti-stick.
2020-07-03 [Wedler] Small refactor so the schematic looks better.
2020-07-05 [Welder] Make the overheat protection a bit nicer.
2020-07-05 [Welder] Add some comments, make it nicer.
2020-07-05 [Welder] Add some article about welder characteristics.
2020-07-05 [Welder] Preliminary work on pin 9 of SG3525.
2020-07-16 [Welder] Add more examples of welding machines.
2020-08-28 [Welder] Improve short circuit simulation: need to have 62V and after some time go down to 5V.
2020-08-28 [Bike] Add some bike photos.
2020-08-28 [Welder] Fix shortcut protection simulation.
2020-08-29 *.log and *.raw from LT Spice are not needed to be under Git control.
2020-08-29 [Welder] Add an idea how to lower the idle voltage from 62V to 31V.
2020-08-29 It looks like *.net from LT SPice is also not needed to be in Git.
2020-09-03 [Welder] Add more info about idea how to lower the idle voltage.
2020-09-09 [Welder] Add an idea how to limit the PWM duty cycle.
2020-09-10 [Welder] Improve SG3525 simulation a bit.
2020-09-10 [Welder] Simulate how to limit the output PWM by using just pin 8 of SG3525.
2020-11-09 [Bike] Add some XCF to see how the bike will look like with different accessories.
2020-11-09 [Welder] Refactor: move sg3525 docs to subfolders.
2020-11-09 [Welder] Add some hardware SG3525 test circuit (they are not for ltspice simulation, they will be used to generate images).
2020-11-10 [Welder] Add some images to generate hardware tests results.
2020-11-10 [Welder] Add more tests circuits.
2020-11-10 [Welder] More description of tests results.
2020-11-11 [Welder] Getting closer to tests results. Just to see if markdown links will work.
2020-11-11 [Welder] Add basic test circuit image.
2020-11-11 [Welder] Add the picture of basic test circuit.
2020-11-11 [Welder] Improve test results doc.
2020-11-11 [Welder] Bugfix in test doc.
2020-11-11 [Welder] Add test results for simple comarator configuration.
2020-11-11 [Welder] Polish the test doc.
2020-11-12 [Welder] Make the images 1024 pixels wide.
2020-11-12 [Welder] Rename the image.
2020-11-12 [Welder] Small fixes in doc.
2020-11-12 [Welder] Add test 2 oscillograms.
2020-11-12 [Welder] Add Test 2 results.
2020-11-13 [Welder] Add oscillograms for tests 3 and 4.
2020-11-13 [Wlder] Add Test 4 results.
2020-11-13 [Welder] Add Test 4 results.
2020-11-16 [Welder] Add more datasheets of SG3525.
2020-11-16 [Welder] Add some possible datasheet relatev to VT1 and VT2 (probably mosfet half-bridges) chips in Power VIP 4000 welding machine.
2020-11-16 [Welder] Add hardware tests of Power VIP 4000 machine.
2020-11-16 [Welder] Add description of tests for Power VIP 4000.
2020-11-16 [Welder] Fixes in tests for Power VIP 4000.
2020-11-21 [Welder] Cosmetic change in description.
2020-11-21 [Welder] Add images for Test 5.
2020-11-21 [Welder] Add Test 5 results.
2020-11-23 [Welder] Add info about variable resistor and its impact to welding current in Magnum Power VIP 4000.
2020-11-23 [Welder] Add some common schematic from https://www.elektroda.pl/rtvforum/topic1699170.html
2020-11-24 [Welder] Add images for Magnum Power VIP 4000 Test 4
2020-11-24 [Welder] Add basic simulation for Magnum POwer VIP 4000 output trafo.
2020-11-24 [Welder] Rename directory with Test 3
2020-11-24 [Welder] Add results of Test 3
2020-11-24 [Welder] Rename directory with Test 2
2020-11-24 [Welder] Add results of Test 2
2020-11-24 [Welder] Rename directory with Test 1
2020-11-24 [Welder] Add results of Test 1
2020-11-24 [Welder] Add main doc about tests.
2020-11-24 [Welder] Divide SG3525A tests into subdirectories.
2020-11-24 [Welder] Copy main test results into subdirectories.
2020-11-24 [Welder] Add tests for SG3525A device.
2020-11-24 [Welder] Add images for Test5.
2020-11-24 [Welder] Add Test5 results.
2020-11-27 [Welder] add more about welders and inverters.
2020-11-27 [Welder] More pictures of Magnum Power VIP 4000.
2020-11-29 [Welder] Add a helpful simulation of transformer driver (downloaded from alaboutcircuits.com)
2020-11-30 [Welder] Add test 6 images.
2020-11-30 [Welder] Add link to Test 5.
2020-11-30 [Welder] Add information about welder not being loaded.
2020-11-30 [Welder] Add test 6 results.
2020-11-30 [Welder] Fixes in test 6 results.
2020-11-30 [Welder] Add reference to Test 6.
2020-12-09 [Distiller] Bill of material.
2020-12-09 [Welder] More input in Test 5.
2021-01-18 [Carburetor] Add instruction hpw to set up carburator in Simson.
2021-01-18 [Distiller] Update BOM.
2021-01-18 [Distiller] Add some articles.
2021-01-18 [Distiller] Rename the file.
2021-01-21 [Distiller] BOM + some info about the destilation + some tables.
2021-01-25 [Welder] Add preliminary Test7 results.
2021-01-25 [Welder] Improve test7.
2021-02-07 [BenchDrill] Some info about my new bench drill.
2021-02-07 [BenchDrill] Add basic document about table-column.
2021-02-07 [BenchDrill] Fix the file name.
2021-02-11 [BenchDrill] Add some images about table-column tests.
2021-02-15 [BenchDrill] Add image.
2021-02-21 [BenchDrill] Add schema image about table-column.
2021-02-21 [BenchDrill] Add images about gilza.
2021-02-21 [OldRadio] Add docs about 'Menuet UKF'
2021-03-11 [Welder] Add idea about 'current setting display'.
2021-03-11 [Distiller] Rework BOM.
2021-03-25 [LTSpice] Basic simulation of npn transistor.
2021-03-25 [Welder] add simulations of potentiometers.
2021-03-25 [Welder] Polish simulations.
2021-04-05 [Distiller] Update BOM
2021-04-05 [Contests] Add various school contests.
2021-04-05 [Welder] Add preliminary schematic and board for current setting display.
2021-04-05 [Distiller] Rename bom into bom_poc (proff of concept).
2021-04-09 [44cats] Add some work on 44cats Kotobirynt.
2021-04-09 [Welder] Add pin9 PWM driver tests results.
2021-04-09 [Welder] Limit PWM with Compensation pin.
2021-04-09 [Welder] Fix description of pin9.
2021-04-14 [Welder] Improve LTSpice description.
2021-04-14 [Welder] Improve schematic.
2021-04-14 [Welder] Add some images.
2021-04-14 [Welder] Refactor: move files to separate folders.
2021-06-21 [BenchDrill] Improve description
2021-06-21 [Contests] Add Kangur 2021
2021-06-22 [Welder] Small fixes in schematics.
2021-06-22 [Welder] Add schematics as images.
2021-06-22 [Welder] Add description about additional display.
2021-06-24 [BenchDrill] Fill measurements.
2021-06-28 [DrillMachine] Add fotos related to 'foot' improvement.
2021-06-29 [BenchDrill] Add info about foot improvement.
2021-06-29 [BenchDrill] Gear box resonance.
2021-06-29 [BenchDrill] Fix link.
2021-06-29 [BenchDrill] Some fixes in description.
2021-06-29 [BenchDrill] Fix typos.
2021-06-29 [BikeScooter] Add file related to the project.
2021-07-01 [BenchDrill] Add photos about reducing casing backlash.
2021-07-01 [BenchDrill] Remove wrong measurement images.
2021-07-01 [BenchDrill] Rename the file.
2021-07-01 [BenchDrill] Rename files so they use underscores.
2021-07-02 [BenchDrill] Add PDF about reducing backlash.
2021-07-02 [BenchDrill] Add picture of test setup.
2021-07-02 [BenchDrill] Add descripption about backlash.
2021-07-03 [Distiller] Update BOM-poc.
2021-07-27 [Bench drill] Add images related to the column.
2021-07-27 [BenchDrill] Usztywnienie kolumny.
2021-07-27 [Distiller] Add info about costs.
2021-08-24 [BenchDrill] Improve description.
2021-10-30 [Distiller] Split BOM into: BOM (production) and BOM poc (proof of concept).
2021-10-30 [Distiller] Add info about collecting 'przedgon' with temperatures meassure.
2021-11-06 [BenchDrill] Improve column.
2021-11-06 [BenchDrill] Improve column. Bugfix in table.
2021-11-06 [BenchDrill] Rework 1.
2021-11-06 [BenchDrill] Rework 3.
2021-11-06 [BenchDrill] Rework 4.
2021-11-06 [BenchDrill] Rework 5.
2021-11-06 [BenchDrill] Bugfix.
2021-12-12 [Distiller] Add image with process 01.
2021-12-12 [Bike] Add image of the bike called 'Trip'.
2021-12-28 [Distiller] Update BOM (almost final version).
2021-12-28 [Distiller] More info about distillation process.
2021-12-28 [BenchDrill] Obrazko do testu odchylenia gondoli.
2021-12-28 [BenchDrill] Pomiar odchylenia gondoli względem kolumny.
2021-12-28 [BenchDrill] Poprawka błedu w tabelce.
2021-12-28 [BenchDrill] Poprawki błędów literowych.
2022-01-04 Create LICENSE
2022-04-04 [Bike] Add bike with nice frame.
2022-04-04 [Contests] Reworks folders.
2022-04-07 [Welder] Add preliminary images on lowering down the idle voltage.
2022-04-08 [Welder] Add description about lowering idle voltage.
2022-04-08 [Welder] Fix typos.
2022-04-10 [Welder] Improve description.
2022-04-11 [Welder] Improve additional test with the bulb.
2022-04-16 [Welder] Improve the 50uA current source on pin 8: it must be marked as an active load.
2022-04-16 [Welder] Improve description on MIG/MAG rework.
2022-04-18 [Welder] Add simulation of lowering idle voltage.
2022-04-18 [Welder] Documentation about lowering idle voltage.
2022-04-19 [Welder] Reorder description about lowering down the idle voltage.
2022-04-19 [Welder] Description about lowering down the idle voltage.
2022-04-21 [Welder] D lowering down tescription abouthe idle voltage.
2022-04-21 [Welder] First photos of flux core MIG welding.
2022-04-21 [Welder] Fix schematic related to the additional potentiometer on pin 8 of SG3525.
2022-04-22 [Welder] Add loopback pin8 voltage driver.
2022-04-26 [Welder] Small correections.
2022-04-26 [Welder] Simulation of voltage regulation with a loopback.
2022-06-08 [Welder] Put more detailed info with measurements.
2022-06-11 [MiniLathe] Add some pictures.
2022-06-21 [MiniLathe] More images.
2022-09-28 [Welder] Preliminary schematics of MMA to MIG improvement.
2022-11-18 [BenchDrill] Add images related to pinola lock.
2022-11-24 [ChocolateFountain] Fix the gear box.
2023-02-18 [Contests] More of Swietlik.
2023-02-25 [Welder] Add images about how to calculate VR1 and VR2.
2023-02-25 [Welder] Fix text layout around the image.
2023-02-25 [Welder] Add note about how to calculate VR1 and VR2.
2024-10-11 [BikeScooter] Preliminary work.
2025-08-05 [LaserCutProjects] Some version of BFF yin-yang pendant.
2025-08-06 [LaserCutProjects] Make it more Lightburn friendly (layers by colors).
2025-09-28 [LaserCutProjects] Update BFF and and scout shield.
2025-10-01 [LaserCutProjects] add Fiat logos and car keychains.
2025-10-01 [LaserCutProjects] Improve BFF yin yang.
2025-10-07 [LaserCutProjects] Dzik key chain.
